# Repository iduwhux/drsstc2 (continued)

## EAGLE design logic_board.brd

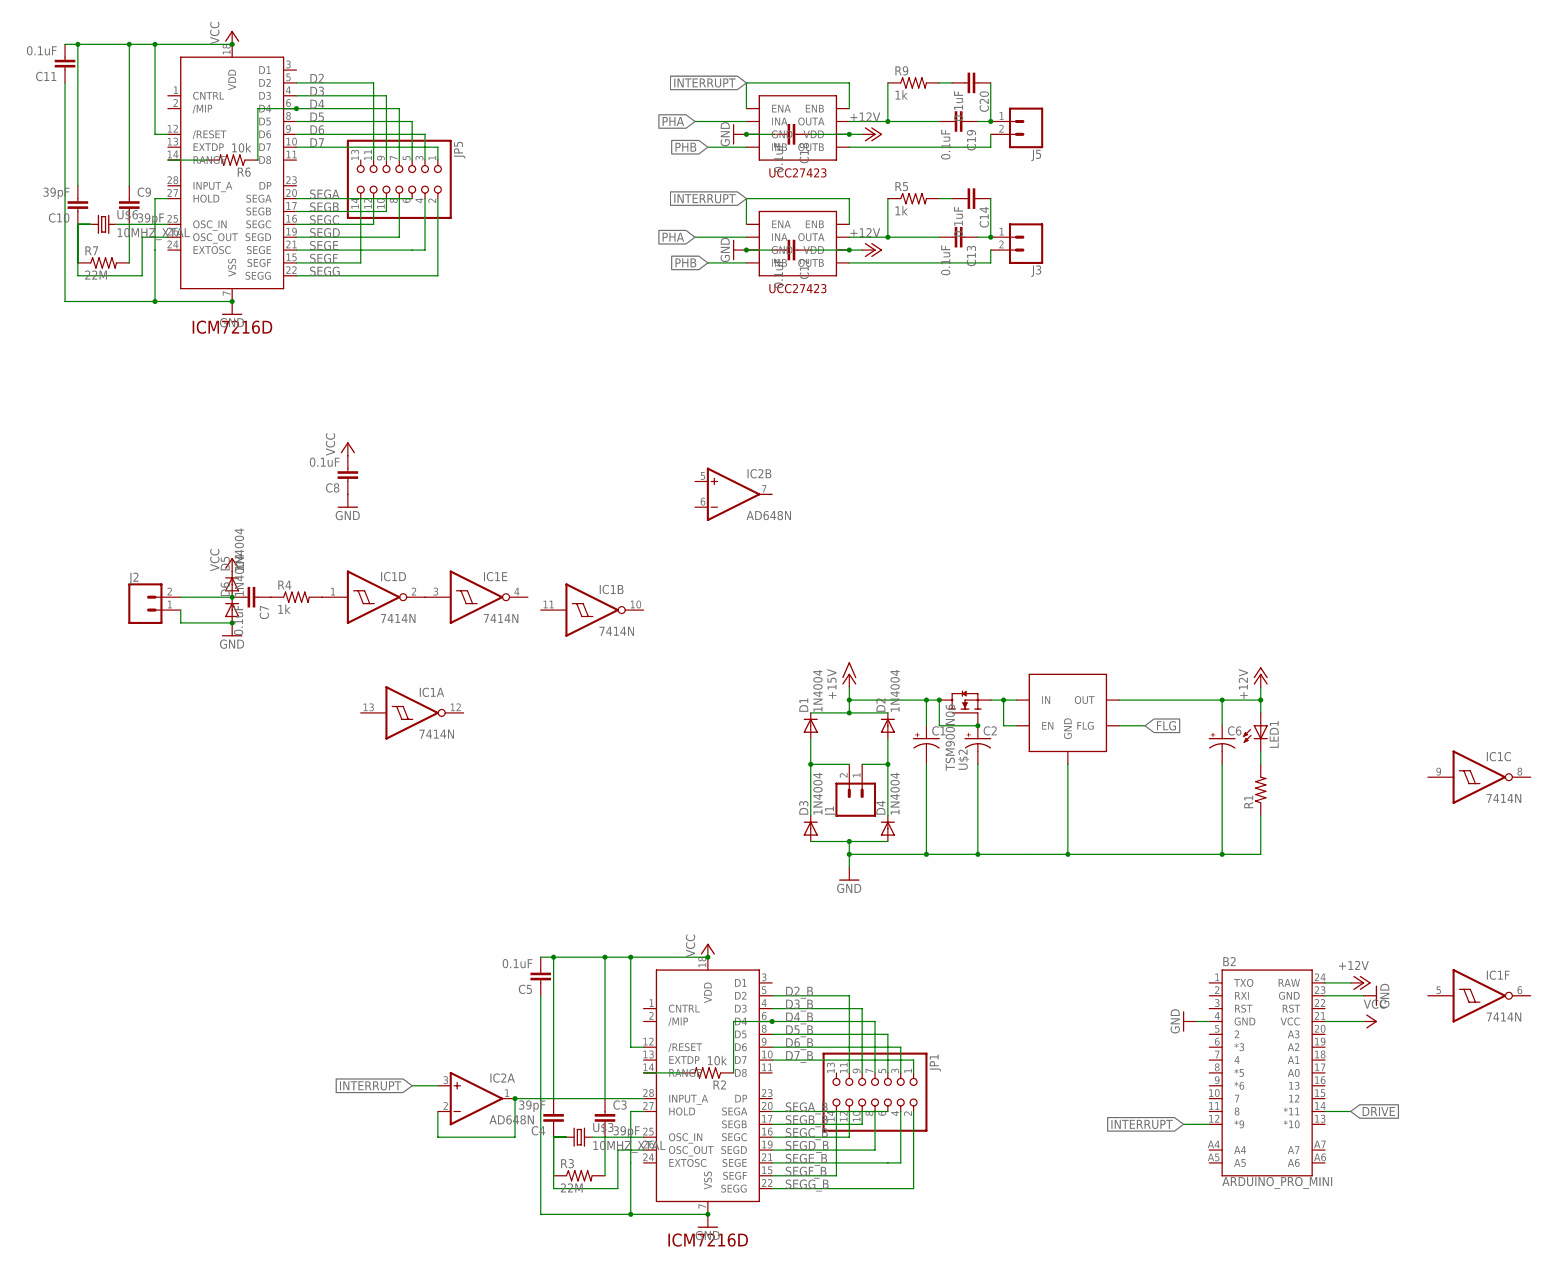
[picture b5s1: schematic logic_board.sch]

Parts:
B2: ARDUINO_PRO_MINI
C1, C2, C6: CPOL-USE7.5-16; E7,5-16
C3, C4, C9, C10: 39pF; C050-030X075
C5, C7, C8, C11, C12, C13, C14, C18, C19, C20: 0.1uF; C050-030X075
D1, D2, D3, D4, D5, D6: 1N4004; DO41-10
IC1: 7414N; DIL14
IC2: AD648N; DIL08
J1, J2, J3, J5: CONN_025MM; SCREWTERMINAL-5MM-2
JP1, JP5: PINHD-2X7; 2X07
LED1: LED5MM
R1: R-US_0204/7; 0204/7
R2, R6: 10k; 0204/7
R3, R7: 22M; 0204/7
R4, R5, R9: 1k; 0204/7
U$1, U$5: ICM7216D; DIP1524W55P254L3740H635Q28B
U$2: TSM900N06; TO-251S
U$3, U$6: 10MHZ_XTAL; XTAL
U$4: MIC29301; TO-220
U$7, U$9: UCC27423; DIP762W53P254L959H508Q8B

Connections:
+12V: B2.24 (RAW), C6.+, C12.1, C18.1, LED1.A, U$4.P$4 (OUT), U$7.6 (VDD), U$9.6 (VDD)
+15V: C1.+, C2.+, D1.C, D2.C, U$2.P$1 (G), U$2.P$2 (D)
D2: JP5.11, U$5.5 (D2)
D2_B: JP1.11, U$1.5 (D2)
D3: JP5.9, U$5.4 (D3)
D3_B: JP1.9, U$1.4 (D3)
D4: JP5.7, R6.1, U$5.6 (D4)
D4_B: JP1.7, R2.1, U$1.6 (D4)
D5: JP5.5, U$5.8 (D5)
D5_B: JP1.5, U$1.8 (D5)
D6: JP5.3, U$5.9 (D6)
D6_B: JP1.3, U$1.9 (D6)
D7: JP5.1, U$5.10 (D7)
D7_B: JP1.1, U$1.10 (D7)
DRIVE: B2.14 (*11)
FLG: U$4.P$5 (FLG)
GND: B2.4 (GND), B2.23 (GND), C1.-, C2.-, C5.1, C6.-, C8.1, C11.1, C12.2, C18.2, D3.A, D4.A, D6.A, IC1.7 (GND), J2.1, R1.1, U$1.7 (VSS), U$1.27 (HOLD), U$4.P$3 (GND), U$5.7 (VSS), U$5.27 (HOLD), U$7.3 (GND), U$9.3 (GND)
INTERRUPT: B2.12 (*9), IC2.3 (+IN), U$7.1 (ENA), U$7.8 (ENB), U$9.1 (ENA), U$9.8 (ENB)
unnamed: D1.A, D3.C, J1.2
unnamed: D2.A, D4.C, J1.1
unnamed: U$2.P$3 (S), U$4.P$1 (EN), U$4.P$2 (IN)
unnamed: LED1.K (C), R1.2
unnamed: C3.2, R3.2, U$1.25 (OSC_IN), U$3.P$2 (2)
unnamed: C4.1, R3.1, U$1.26 (OSC_OUT), U$3.P$1 (1)
unnamed: C7.2, D5.A, D6.C, J2.2
unnamed: C13.1, C14.1, J3.1
unnamed: C7.1, R4.1
unnamed: R2.2, U$1.14 (RANGE)
unnamed: R6.2, U$5.14 (RANGE)
unnamed: C9.2, R7.2, U$5.25 (OSC_IN), U$6.P$2 (2)
unnamed: C10.1, R7.1, U$5.26 (OSC_OUT), U$6.P$1 (1)
unnamed: IC1.1 (I), R4.2
unnamed: IC1.2 (O), IC1.3 (I)
unnamed: C14.2, R5.2
unnamed: C13.2, R5.1, U$7.7 (OUTA)
unnamed: J3.2, U$7.5 (OUTB)
unnamed: IC2.1 (OUT), IC2.2 (-IN), U$1.28 (INPUT_A)
unnamed: C19.1, C20.1, J5.1
unnamed: C20.2, R9.2
unnamed: C19.2, R9.1, U$9.7 (OUTA)
unnamed: J5.2, U$9.5 (OUTB)
PHA: U$7.2 (INA), U$9.2 (INA)
PHB: U$7.4 (INB), U$9.4 (INB)
SEGA: JP5.6, U$5.20 (SEGA)
SEGA_B: JP1.6, U$1.20 (SEGA)
SEGB: JP5.10, U$5.17 (SEGB)
SEGB_B: JP1.10, U$1.17 (SEGB)
SEGC: JP5.12, U$5.16 (SEGC)
SEGC_B: JP1.12, U$1.16 (SEGC)
SEGD: JP5.8, U$5.19 (SEGD)
SEGD_B: JP1.8, U$1.19 (SEGD)
SEGE: JP5.4, U$5.21 (SEGE)
SEGE_B: JP1.4, U$1.21 (SEGE)
SEGF: JP5.14, U$5.15 (SEGF)
SEGF_B: JP1.14, U$1.15 (SEGF)
SEGG: JP5.2, U$5.22 (SEGG)
SEGG_B: JP1.2, U$1.22 (SEGG)
V+: IC2.8 (V+)
V-: IC2.4 (V-)
VCC: B2.21 (VCC), C3.1, C4.2, C5.2, C8.2, C9.1, C10.2, C11.2, D5.C, IC1.14 (VCC), U$1.12 (/RESET), U$1.18 (VDD), U$5.12 (/RESET), U$5.18 (VDD)

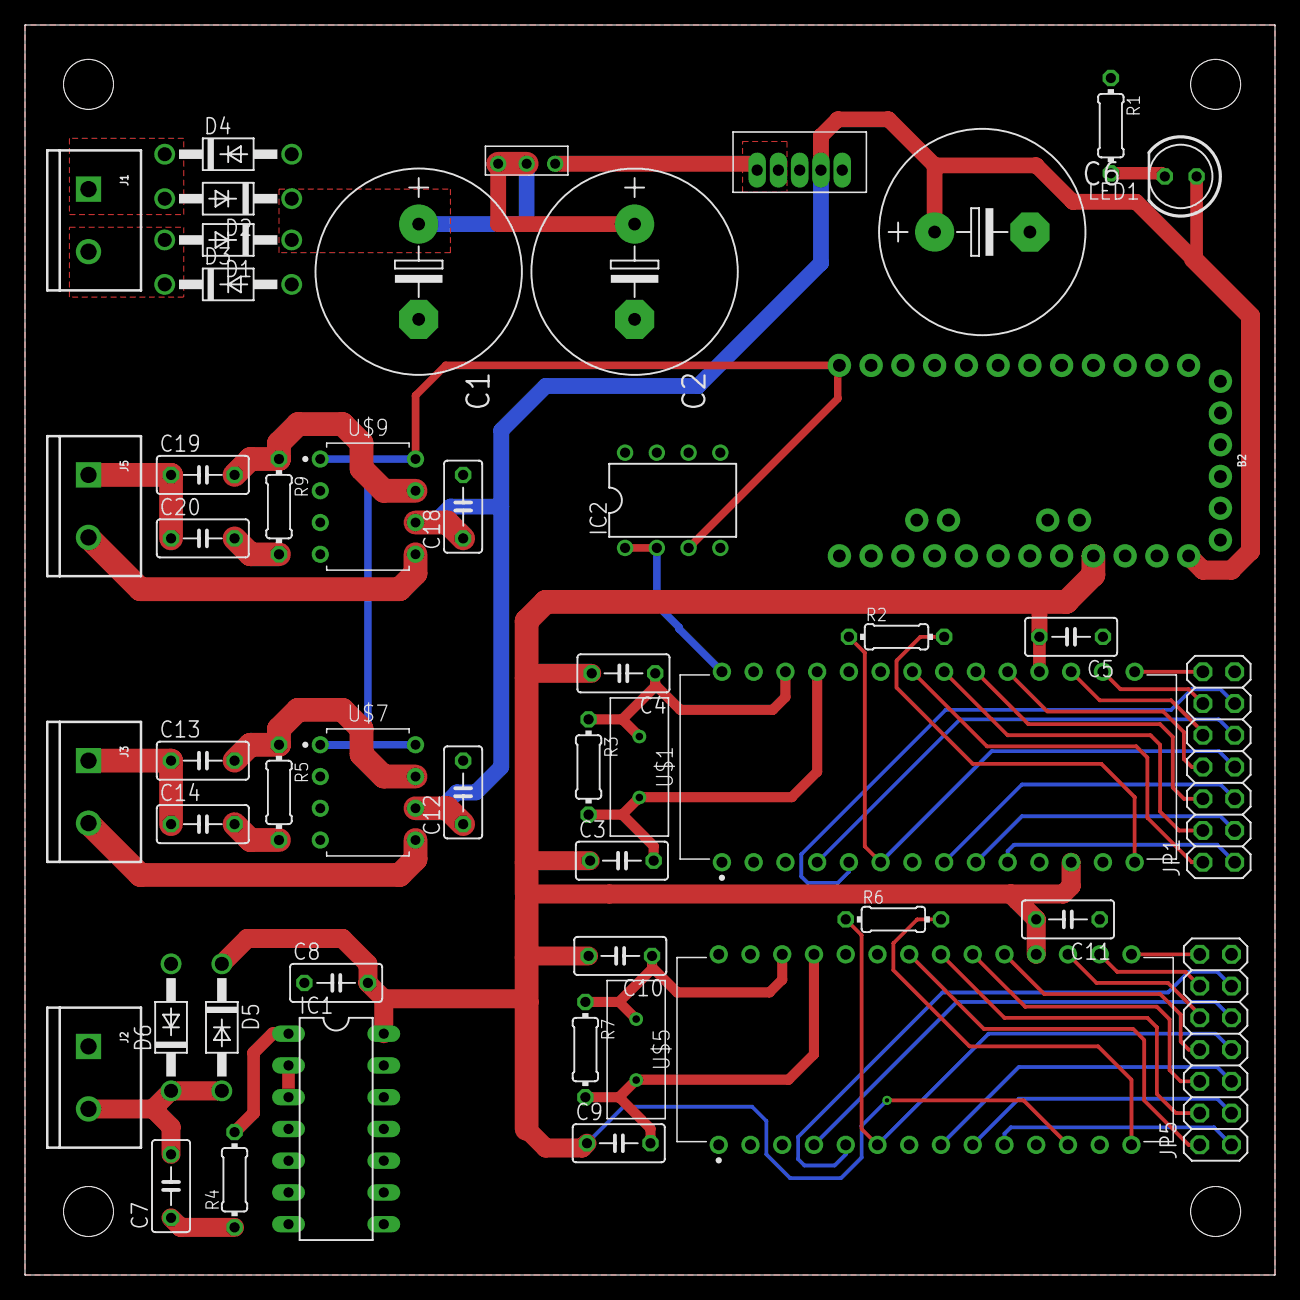
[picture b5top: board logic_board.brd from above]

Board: 2 copper layers, 100.0 x 100.0 mm, 49 parts (0 on the bottom side), 56 nets.

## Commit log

2019-03-26 Updating files and .gitignore
2019-03-26 Adding RF shield patterns
2019-03-26 Adding switch_board
2019-03-26 Adding switch housing acrylic laser patterns
2019-03-26 Adding board_test Arduino sketch
2019-03-26 Adding drsstc_firmware
2019-03-26 Adding TO-247 step model
2019-03-26 Adding rev A board orders
2019-03-26 Adding FreqCalcs Excel spreadsheet
2019-03-26 Adding bmp.scr
2019-03-26 Updating firmware
2019-03-27 Adding TestCuts.svg
2019-03-27 Updating DXFs for acrylic with smaller kerf offset
2019-03-31 Updating DRSSTC board to Rev B
2019-03-31 Adding strandtest
2019-03-31 Updating Rev B board, linking freq counter to driver input signal
2019-03-31 Updating CVM logo
2019-03-31 Updating firmware with pulsed test mode
2019-03-31 Cleaning up firmware
2019-03-31 Moving LightShow.cpp code to LEDRing.cpp
2019-03-31 Continuing firmware cleanup
2019-03-31 Continuing firmware cleanup, adding LED rotation support to MIDI binary
2019-03-31 Reorganizing firmware, cleaning up MIDIPlayer.h
2019-03-31 More firmware cleanup
2019-04-12 Updating Rev B board with hysteresis feedback fix
2019-04-14 Rev B board
2019-04-14 Rev B silkscreen tweak
2019-05-31 Updating image
2019-05-31 Adding GDT booster board
2019-05-31 Adding GDT booster CAM job and order to JLC PCB
2019-05-31 Adding airflow cover stuff to laser folder
2019-05-31 Updating .gitignore
2019-05-31 Adding PDF schematics
2019-05-31 Adding layout.svg
2019-06-01 Adding laser pattern for acrylic
2019-06-07 Adding side panel files for laser
2019-06-07 Removing teslacoil.l#* files
2019-06-07 Updating .gitignore to ignore *.l#* files
2019-06-07 Adding 3D printing STL files for booster and logic board mounts
2019-06-10 Adding bus bar files
2019-06-12 Adding control_box files for laser
2019-06-12 Adding fuse support parts to control box laser
2019-06-16 Updating firmware, adding variable length test mode
2019-06-16 Updating control box laser outline
2019-06-16 Adding more songs to firmware
2019-06-16 Adding MIDI converter Jupyter notebook and MIDI files
2019-06-16 Adding midi_converter/.gitignore
2019-06-17 Updating midi_converter with WAV simulator
2019-06-17 Factoring out arduino_midi module
2019-06-17 Updating firmware with converted MIDI files, as well as updating midi_converter
2019-06-17 Updating firmware/midi_converter
2019-06-17 Adding sugar plum fairy, randomizing song order
2019-06-18 Adding serial logging and a metronome
2019-06-20 Updating from labtop
2019-06-20 Updating control box top
2019-06-20 Adding control_box_top.svg
2019-06-22 Updating firmware, clearing out complex LED code
2019-06-22 Removing LED instruction case from MIDI handler
2019-06-22 Adding some simple LED animations
2019-06-22 Adding more songs
2019-06-22 Adding song_name for bach invention
2019-06-22 Fixing tgt_duty calculation
2019-06-22 Adjusting volume calculation in MIDI firmware
2019-06-22 Updating WAV simulator to account for 'true' on time
2019-06-22 Updating volume mapping in midi converter
2019-06-23 Removing extra song files
2019-06-23 Cleanup firmware
2019-06-23 Adding serial heartbeat message
2019-06-23 Increasing SERIAL_HEARBEAT_TIME
